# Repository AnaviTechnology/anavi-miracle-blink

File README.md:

# ANAVI Miracle Blink

Tiny open source hardware IoT for controlling addressable RGB LED strips (like WS2812B) with XIAO ESP32C3, I2C sensors and mini OLED display.

# License

The project is released under the [Creative Commons Attribution-ShareAlike 4.0 International (CC BY-SA 4.0)](https://creativecommons.org/licenses/by-sa/4.0/).

Note: This is a human-readable summary of (and not a substitute for) the [license](https://creativecommons.org/licenses/by-sa/4.0/legalcode).

You are free to:

Share — copy and redistribute the material in any medium or format Adapt — remix, transform, and build upon the material for any purpose, even commercially. The licensor cannot revoke these freedoms as long as you follow the license terms. Under the following terms:

Attribution — You must give appropriate credit, provide a link to the license, and indicate if changes were made. You may do so in any reasonable manner, but not in any way that suggests the licensor endorses you or your use. ShareAlike — If you remix, transform, or build upon the material, you must distribute your contributions under the same license as the original. No additional restrictions — You may not apply legal terms or technological measures that legally restrict others from doing anything the license permits. Notices:

You do not have to comply with the license for elements of the material in the public domain or where your use is permitted by an applicable exception or limitation. No warranties are given. The license may not give you all of the permissions necessary for your intended use. For example, other rights such as publicity, privacy, or moral rights may limit how you use the material.

You will have to provide a link to the original creator of the project http://www.anavi.technology on any documentation or website.

Credit can be attributed through a link to the creator website: http://www.anavi.technology

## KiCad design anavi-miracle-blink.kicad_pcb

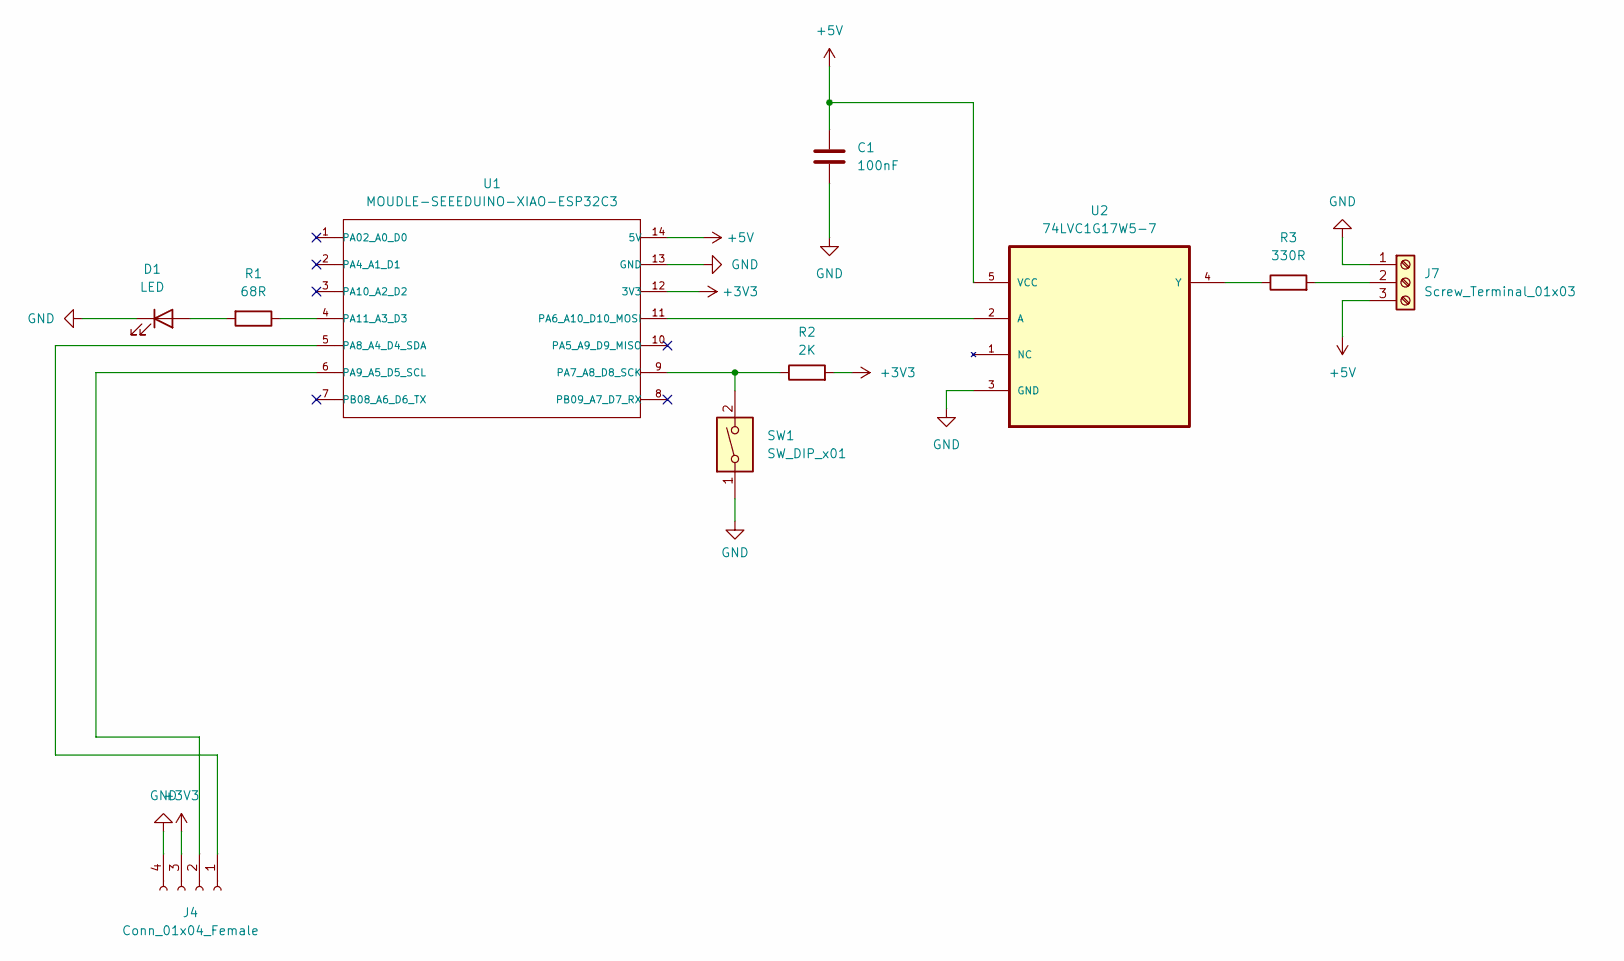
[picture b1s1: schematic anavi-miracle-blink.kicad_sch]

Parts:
C1: 100nF; C_0603_1608Metric_Pad1.08x0.95mm_HandSolder
D1: LED; LED_1206_3216Metric
J4: Conn_01x04_Female; PinHeader_1x04_P2.54mm_Vertical
J7: Screw_Terminal_01x03; TerminalBlock_Phoenix_MKDS-1,5-3_1x03_P5.00mm_Horizontal
R1: 68R; R_0603_1608Metric_Pad0.98x0.95mm_HandSolder
R2: 2K; R_0603_1608Metric_Pad0.98x0.95mm_HandSolder
R3: 330R; R_0603_1608Metric_Pad0.98x0.95mm_HandSolder
SW1: SW_DIP_x01; SW_PUSH_6mm_H4.3mm
U1: MOUDLE-SEEEDUINO-XIAO-ESP32C3; MOUDLE14P-SMD-2.54-21X17.8MM
U2: 74LVC1G17W5-7; SOT95P280X145-5N; MPN 74LVC1G17W5-7

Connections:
+3V3: J4.3, R2.2, U1.12 (3V3)
+5V: C1.1, J7.3, U1.14 (5V), U2.5 (VCC)
GND: C1.2, D1.1 (K), J4.4, J7.1, SW1.1, U1.13 (GND), U2.3 (GND)
unnamed: D1.2 (A), R1.2
unnamed: J4.1, U1.5 (PA8_A4_D4_SDA)
unnamed: J4.2, U1.6 (PA9_A5_D5_SCL)
unnamed: J7.2, R3.2
unnamed: U1.11 (PA6_A10_D10_MOSI), U2.2 (A)
unnamed: R2.1, SW1.2, U1.9 (PA7_A8_D8_SCK)
unnamed: R1.1, U1.4 (PA11_A3_D3)
unnamed: R3.1, U2.4 (Y)

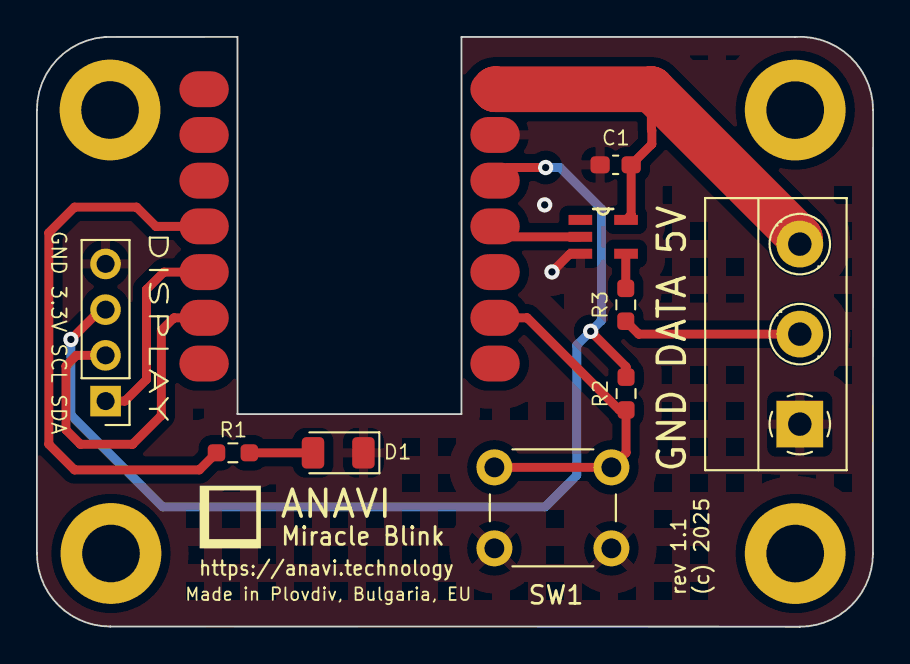
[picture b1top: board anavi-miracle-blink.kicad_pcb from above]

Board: 2 copper layers, 46.5 x 32.8 mm, 10 parts (0 on the bottom side), 11 nets.

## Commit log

2025-06-04 Rev 1.1: Remove Schottky diode
    Remove Schottky diode to allow using the USB-C as power source for
    NeoPixel LEDs. The Schottky diode can still be added externally in
    the use case of external 5V power supply.

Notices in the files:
anavi-miracle-blink.kicad_pcb:
(c) 2025
